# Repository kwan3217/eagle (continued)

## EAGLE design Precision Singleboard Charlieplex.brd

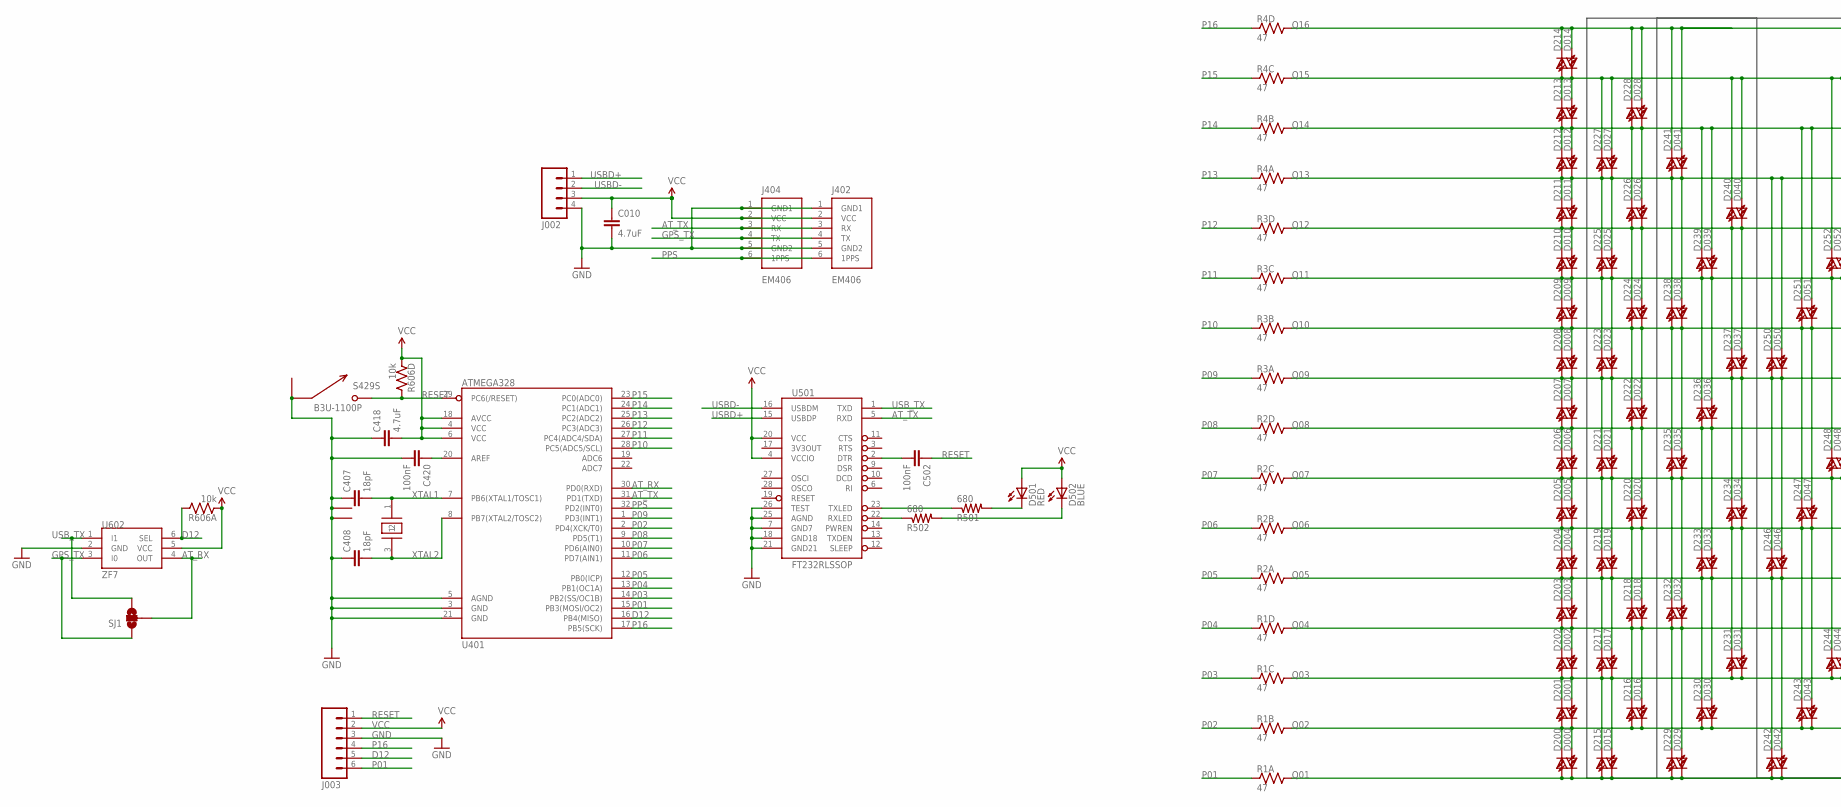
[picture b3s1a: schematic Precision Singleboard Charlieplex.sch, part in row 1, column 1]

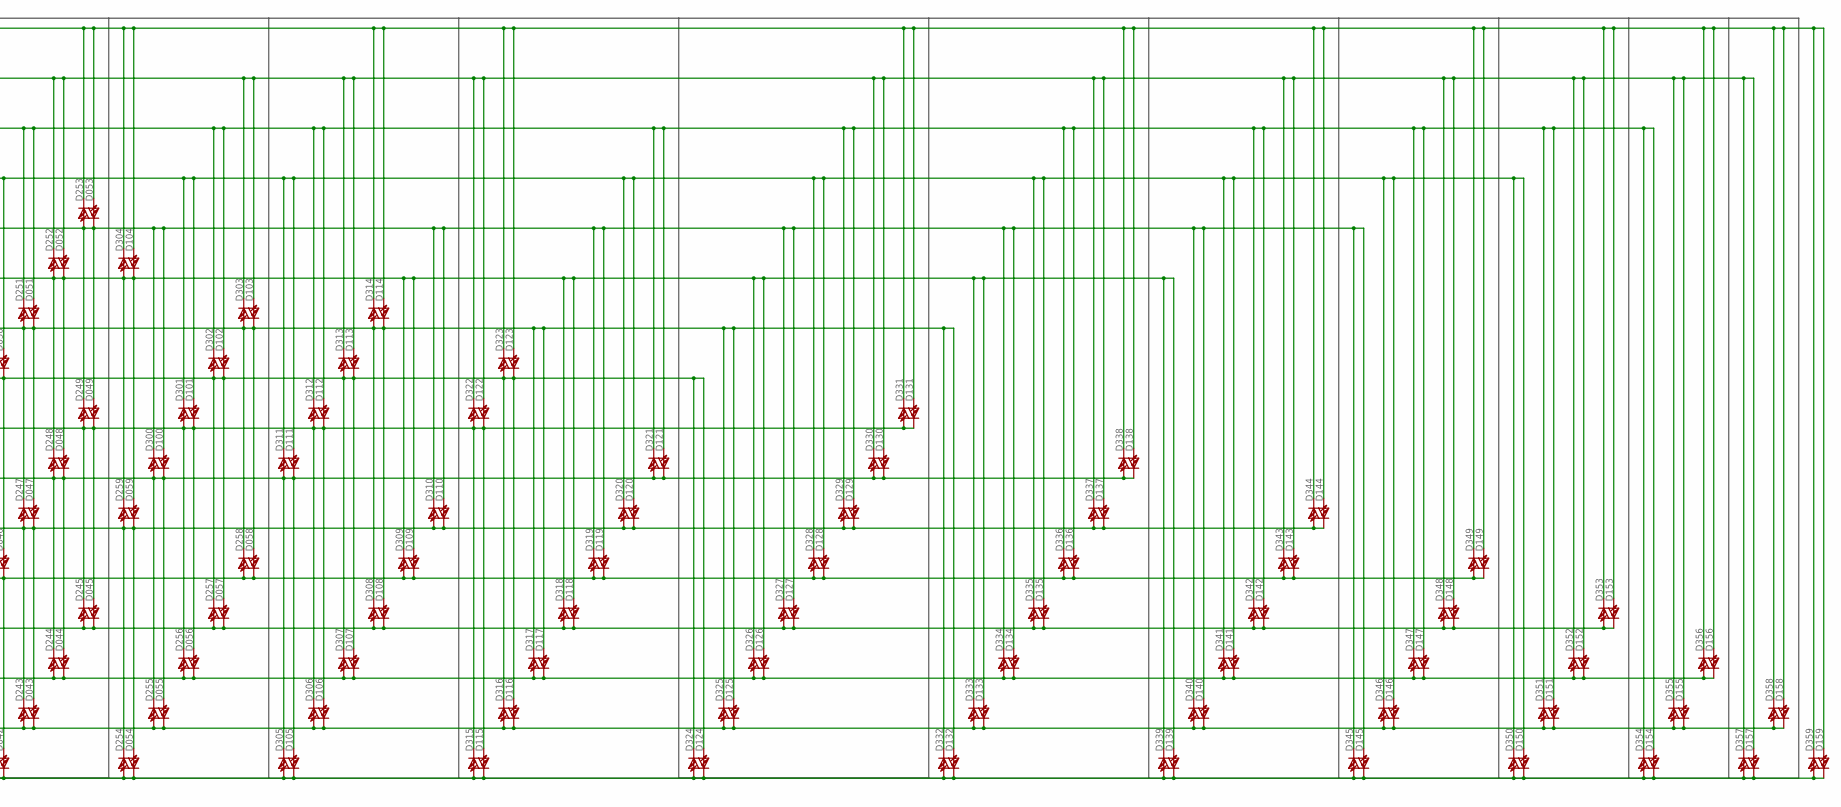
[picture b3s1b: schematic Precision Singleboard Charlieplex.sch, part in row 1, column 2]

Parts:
C010, C418: 4.7uF; 0603-CAP
C407, C408: 18pF; 0603-CAP
C420, C502: 100nF; 0603-CAP
D000, D001, D002, D003, D004, D005, D006, D007, D008, D009, D010, D011, D012, D013, D014, D015, D016, D017, D018, D019, D020, D021, D022, D023, D024, D025, D026, D027, D028, D029, D030, D031, D032, D033, D034, D035, D036, D037, D038, D039, D040, D041, D042, D043, D044, D045, D046, D047, D048, D049, D050, D051, D052, D053, D054, D055, D056, D057, D058, D059, D100, D101, D102, D103, D104, D105, D106, D107, D108, D109, D110, D111, D112, D113, D114, D115, D116, D117, D118, D119, D120, D121, D122, D123, D124, D125, D126, D127, D128, D129, D130, D131, D132, D133, D134, D135, D136, D137, D138, D139, D140, D141, D142, D143, D144, D145, D146, D147, D148, D149, D150, D151, D152, D153, D154, D155, D156, D157, D158, D159, D200, D201, D202, D203, D204, D205, D206, D207, D208, D209, D210, D211, D212, D213, D214, D215, D216, D217, D218, D219, D220, D221, D222, D223, D224, D225, D226, D227, D228, D229, D230, D231, D232, D233, D234, D235, D236, D237, D238, D239, D240, D241, D242, D243, D244, D245, D246, D247, D248, D249, D250, D251, D252, D253, D254, D255, D256, D257, D258, D259, D300, D301, D302, D303, D304, D305, D306, D307, D308, D309, D310, D311, D312, D313, D314, D315, D316, D317, D318, D319, D320, D321, D322, D323, D324, D325, D326, D327, D328, D329, D330, D331, D332, D333, D334, D335, D336, D337, D338, D339, D340, D341, D342, D343, D344, D345, D346, D347, D348, D349, D350, D351, D352, D353, D354, D355, D356, D357, D358, D359: HOUR; LED-0603
D501: RED; LED-0603
D502: BLUE; LED-0603
J002: M04PTH; 1X04
J003: M06SIP; 1X06
J402, J404: EM406
R1, R2, R3, R4: 47; CRA04
R501, R502: 680; 0603-RES
R606: 10k; CRA04
S429: B3U-1100P
SJ1: SOLDERJUMPER_2WAYS; SJ_3
U401: ATMEGA328; TQFP32-08
U501: FT232RLSSOP; SSOP28DB
U602: ZF7; SC-70-6
Y401: 12.00; CRYSTAL_SMD

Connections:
AREF: C420.1, U401.20 (AREF)
AT_RX: SJ1.2, U401.30 (PD0(RXD)), U602.4 (OUT)
AT_TX: J402.3 (RX), J404.3 (RX), U401.31 (PD1(TXD)), U501.5 (RXD)
D12: J003.5, R606.8 (2), U401.16 (PB4(MISO)), U602.6 (SEL)
GND: C010.2, C407.1, C408.1, C418.1, C420.2, J002.4, J003.3, J402.1 (GND1), J402.5 (GND2), J404.1 (GND1), J404.5 (GND2), S429.P$1 (1), S429.P$3 (1), U401.3 (GND), U401.5 (AGND), U401.21 (GND), U501.7 (GND7), U501.18 (GND18), U501.21 (GND21), U501.25 (AGND), U501.26 (TEST), U602.2 (GND), Y401.2 (1), Y401.4 (1)
GPS_TX: J402.4 (TX), J404.4 (TX), SJ1.1, U602.3 (I0)
unnamed: C502.2, U501.2 (DTR)
unnamed: D501.C, R501.2
unnamed: R501.1, U501.23 (TXLED)
unnamed: R502.1, U501.22 (RXLED)
unnamed: D502.C, R502.2
P01: J003.6, R1.1, U401.15 (PB3(MOSI/OC2))
P02: R1.2 (1), U401.2 (PD4(XCK/T0))
P03: R1.3 (1), U401.14 (PB2(SS/OC1B))
P04: R1.4 (1), U401.13 (PB1(OC1A))
P05: R2.1, U401.12 (PB0(ICP))
P06: R2.2 (1), U401.11 (PD7(AIN1))
P07: R2.3 (1), U401.10 (PD6(AIN0))
P08: R2.4 (1), U401.9 (PD5(T1))
P09: R3.1, U401.1 (PD3(INT1))
P10: R3.2 (1), U401.28 (PC5(ADC5/SCL))
P11: R3.3 (1), U401.27 (PC4(ADC4/SDA))
P12: R3.4 (1), U401.26 (PC3(ADC3))
P13: R4.1, U401.25 (PC2(ADC2))
P14: R4.2 (1), U401.24 (PC1(ADC1))
P15: R4.3 (1), U401.23 (PC0(ADC0))
P16: J003.4, R4.4 (1), U401.17 (PB5(SCK))
PPS: J402.6 (1PPS), J404.6 (1PPS), U401.32 (PD2(INT0))
Q01: D000.C, D015.C, D029.C, D042.C, D054.C, D105.C, D115.C, D124.C, D132.C, D139.C, D145.C, D150.C, D154.C, D157.C, D159.C, D200.A, D215.A, D229.A, D242.A, D254.A, D305.A, D315.A, D324.A, D332.A, D339.A, D345.A, D350.A, D354.A, D357.A, D359.A, R1.8 (2)
Q02: D000.A, D001.C, D016.C, D030.C, D043.C, D055.C, D106.C, D116.C, D125.C, D133.C, D140.C, D146.C, D151.C, D155.C, D158.C, D200.C, D201.A, D216.A, D230.A, D243.A, D255.A, D306.A, D316.A, D325.A, D333.A, D340.A, D346.A, D351.A, D355.A, D358.A, R1.7 (2)
Q03: D001.A, D002.C, D015.A, D017.C, D031.C, D044.C, D056.C, D107.C, D117.C, D126.C, D134.C, D141.C, D147.C, D152.C, D156.C, D201.C, D202.A, D215.C, D217.A, D231.A, D244.A, D256.A, D307.A, D317.A, D326.A, D334.A, D341.A, D347.A, D352.A, D356.A, R1.6 (2)
Q04: D002.A, D003.C, D016.A, D018.C, D029.A, D032.C, D045.C, D057.C, D108.C, D118.C, D127.C, D135.C, D142.C, D148.C, D153.C, D202.C, D203.A, D216.C, D218.A, D229.C, D232.A, D245.A, D257.A, D308.A, D318.A, D327.A, D335.A, D342.A, D348.A, D353.A, R1.5 (2)
Q05: D003.A, D004.C, D017.A, D019.C, D030.A, D033.C, D042.A, D046.C, D058.C, D109.C, D119.C, D128.C, D136.C, D143.C, D149.C, D203.C, D204.A, D217.C, D219.A, D230.C, D233.A, D242.C, D246.A, D258.A, D309.A, D319.A, D328.A, D336.A, D343.A, D349.A, R2.8 (2)
Q06: D004.A, D005.C, D018.A, D020.C, D031.A, D034.C, D043.A, D047.C, D054.A, D059.C, D110.C, D120.C, D129.C, D137.C, D144.C, D204.C, D205.A, D218.C, D220.A, D231.C, D234.A, D243.C, D247.A, D254.C, D259.A, D310.A, D320.A, D329.A, D337.A, D344.A, R2.7 (2)
Q07: D005.A, D006.C, D019.A, D021.C, D032.A, D035.C, D044.A, D048.C, D055.A, D100.C, D105.A, D111.C, D121.C, D130.C, D138.C, D205.C, D206.A, D219.C, D221.A, D232.C, D235.A, D244.C, D248.A, D255.C, D300.A, D305.C, D311.A, D321.A, D330.A, D338.A, R2.6 (2)
Q08: D006.A, D007.C, D020.A, D022.C, D033.A, D036.C, D045.A, D049.C, D056.A, D101.C, D106.A, D112.C, D115.A, D122.C, D131.C, D206.C, D207.A, D220.C, D222.A, D233.C, D236.A, D245.C, D249.A, D256.C, D301.A, D306.C, D312.A, D315.C, D322.A, D331.A, R2.5 (2)
Q09: D007.A, D008.C, D021.A, D023.C, D034.A, D037.C, D046.A, D050.C, D057.A, D102.C, D107.A, D113.C, D116.A, D123.C, D124.A, D207.C, D208.A, D221.C, D223.A, D234.C, D237.A, D246.C, D250.A, D257.C, D302.A, D307.C, D313.A, D316.C, D323.A, D324.C, R3.8 (2)
Q10: D008.A, D009.C, D022.A, D024.C, D035.A, D038.C, D047.A, D051.C, D058.A, D103.C, D108.A, D114.C, D117.A, D125.A, D132.A, D208.C, D209.A, D222.C, D224.A, D235.C, D238.A, D247.C, D251.A, D258.C, D303.A, D308.C, D314.A, D317.C, D325.C, D332.C, R3.7 (2)
Q11: D009.A, D010.C, D023.A, D025.C, D036.A, D039.C, D048.A, D052.C, D059.A, D104.C, D109.A, D118.A, D126.A, D133.A, D139.A, D209.C, D210.A, D223.C, D225.A, D236.C, D239.A, D248.C, D252.A, D259.C, D304.A, D309.C, D318.C, D326.C, D333.C, D339.C, R3.6 (2)
Q12: D010.A, D011.C, D024.A, D026.C, D037.A, D040.C, D049.A, D053.C, D100.A, D110.A, D119.A, D127.A, D134.A, D140.A, D145.A, D210.C, D211.A, D224.C, D226.A, D237.C, D240.A, D249.C, D253.A, D300.C, D310.C, D319.C, D327.C, D334.C, D340.C, D345.C, R3.5 (2)
Q13: D011.A, D012.C, D025.A, D027.C, D038.A, D041.C, D050.A, D101.A, D111.A, D120.A, D128.A, D135.A, D141.A, D146.A, D150.A, D211.C, D212.A, D225.C, D227.A, D238.C, D241.A, D250.C, D301.C, D311.C, D320.C, D328.C, D335.C, D341.C, D346.C, D350.C, R4.8 (2)
Q14: D012.A, D013.C, D026.A, D028.C, D039.A, D051.A, D102.A, D112.A, D121.A, D129.A, D136.A, D142.A, D147.A, D151.A, D154.A, D212.C, D213.A, D226.C, D228.A, D239.C, D251.C, D302.C, D312.C, D321.C, D329.C, D336.C, D342.C, D347.C, D351.C, D354.C, R4.7 (2)
Q15: D013.A, D014.C, D027.A, D040.A, D052.A, D103.A, D113.A, D122.A, D130.A, D137.A, D143.A, D148.A, D152.A, D155.A, D157.A, D213.C, D214.A, D227.C, D240.C, D252.C, D303.C, D313.C, D322.C, D330.C, D337.C, D343.C, D348.C, D352.C, D355.C, D357.C, R4.6 (2)
Q16: D014.A, D028.A, D041.A, D053.A, D104.A, D114.A, D123.A, D131.A, D138.A, D144.A, D149.A, D153.A, D156.A, D158.A, D159.A, D214.C, D228.C, D241.C, D253.C, D304.C, D314.C, D323.C, D331.C, D338.C, D344.C, D349.C, D353.C, D356.C, D358.C, D359.C, R4.5 (2)
RESET: C502.1, J003.1, R606.5 (2), S429.P$2 (2), U401.29 (PC6(/RESET))
USBD+: J002.1, U501.15 (USBDP)
USBD-: J002.2, U501.16 (USBDM)
USB_TX: SJ1.3, U501.1 (TXD), U602.1 (I1)
VCC: C010.1, C418.2, D501.A, D502.A, J002.3, J003.2, J402.2 (VCC), J404.2 (VCC), R606.1, R606.4 (1), U401.4 (VCC), U401.6 (VCC), U401.18 (AVCC), U501.4 (VCCIO), U501.20 (VCC), U602.5 (VCC)
XTAL1: C407.2, U401.7 (PB6(XTAL1/TOSC1)), Y401.1
XTAL2: C408.2, U401.8 (PB7(XTAL2/TOSC2)), Y401.3 (2)

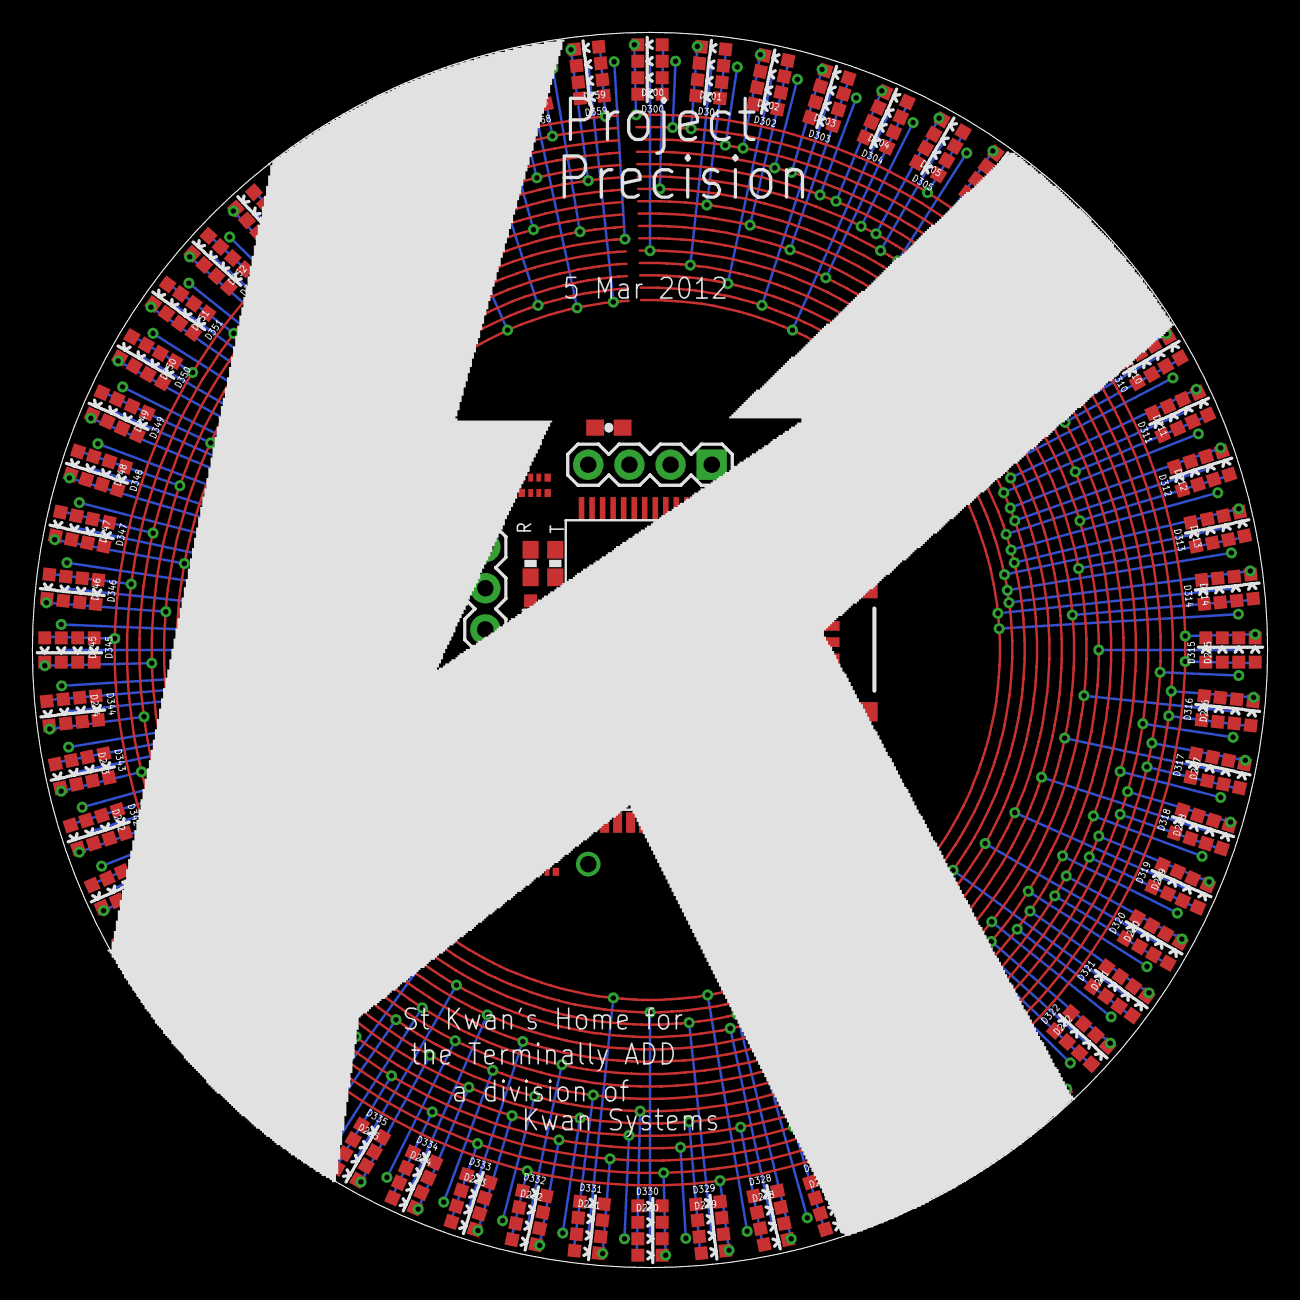
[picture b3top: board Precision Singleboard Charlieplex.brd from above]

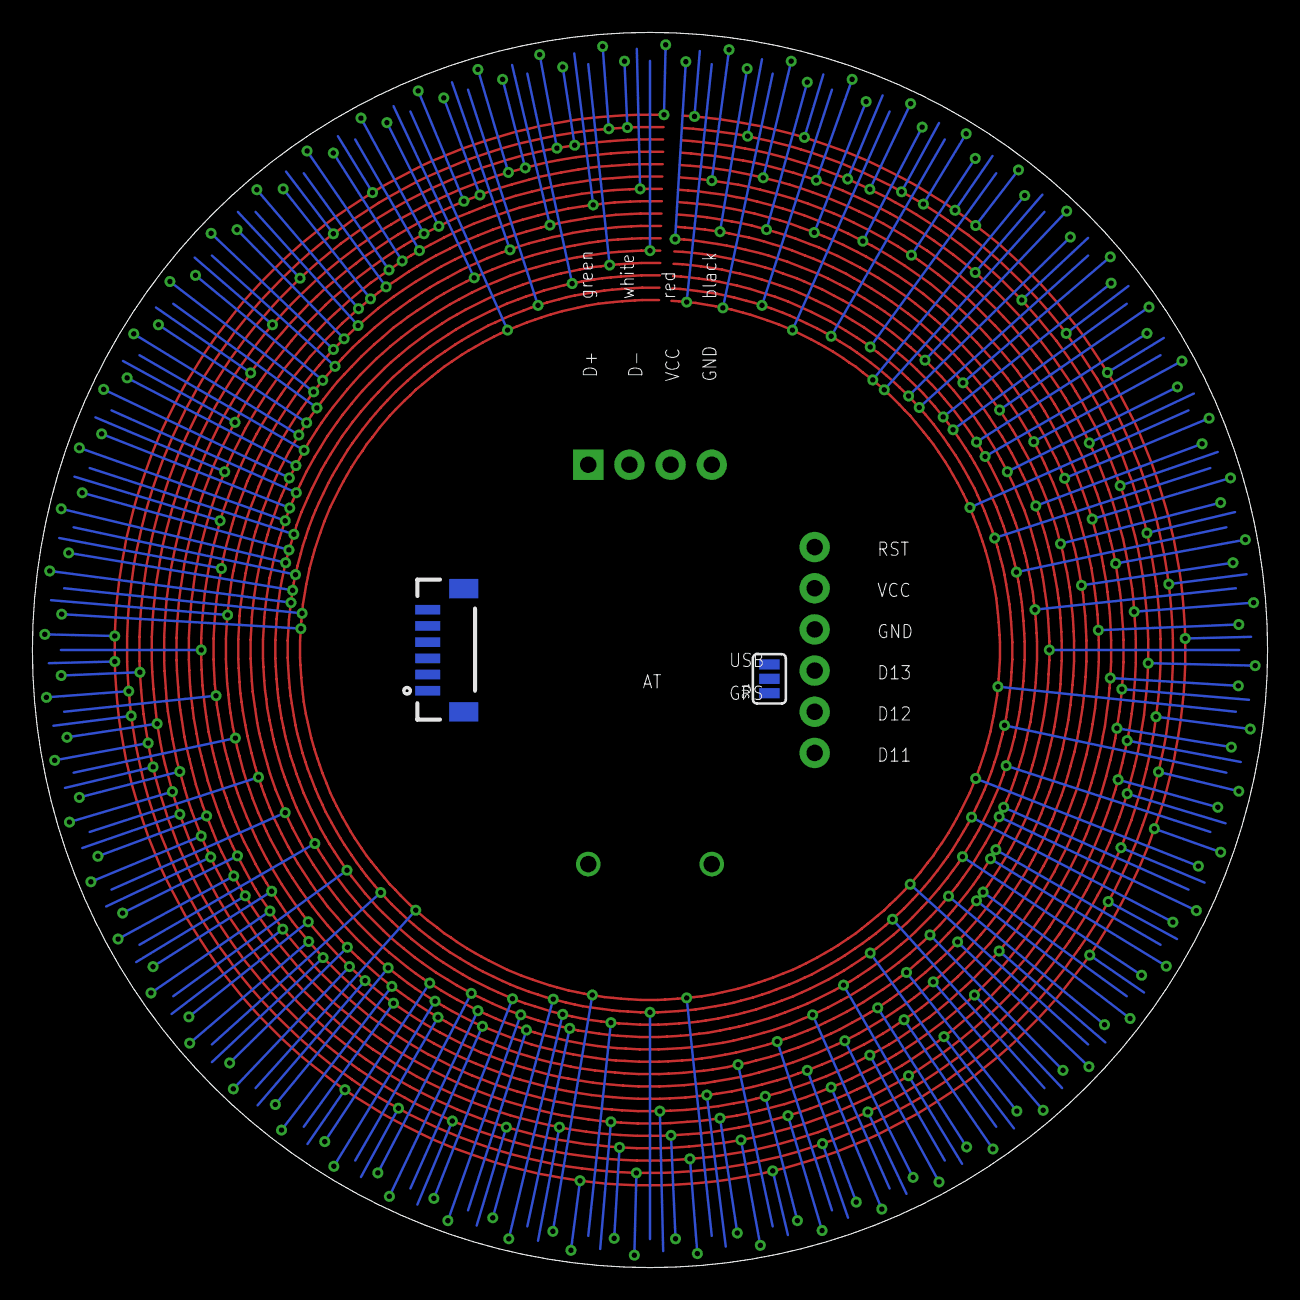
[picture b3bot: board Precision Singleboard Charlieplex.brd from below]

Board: 2 copper layers, 76.2 x 76.2 mm, 265 parts (2 on the bottom side), 51 nets.

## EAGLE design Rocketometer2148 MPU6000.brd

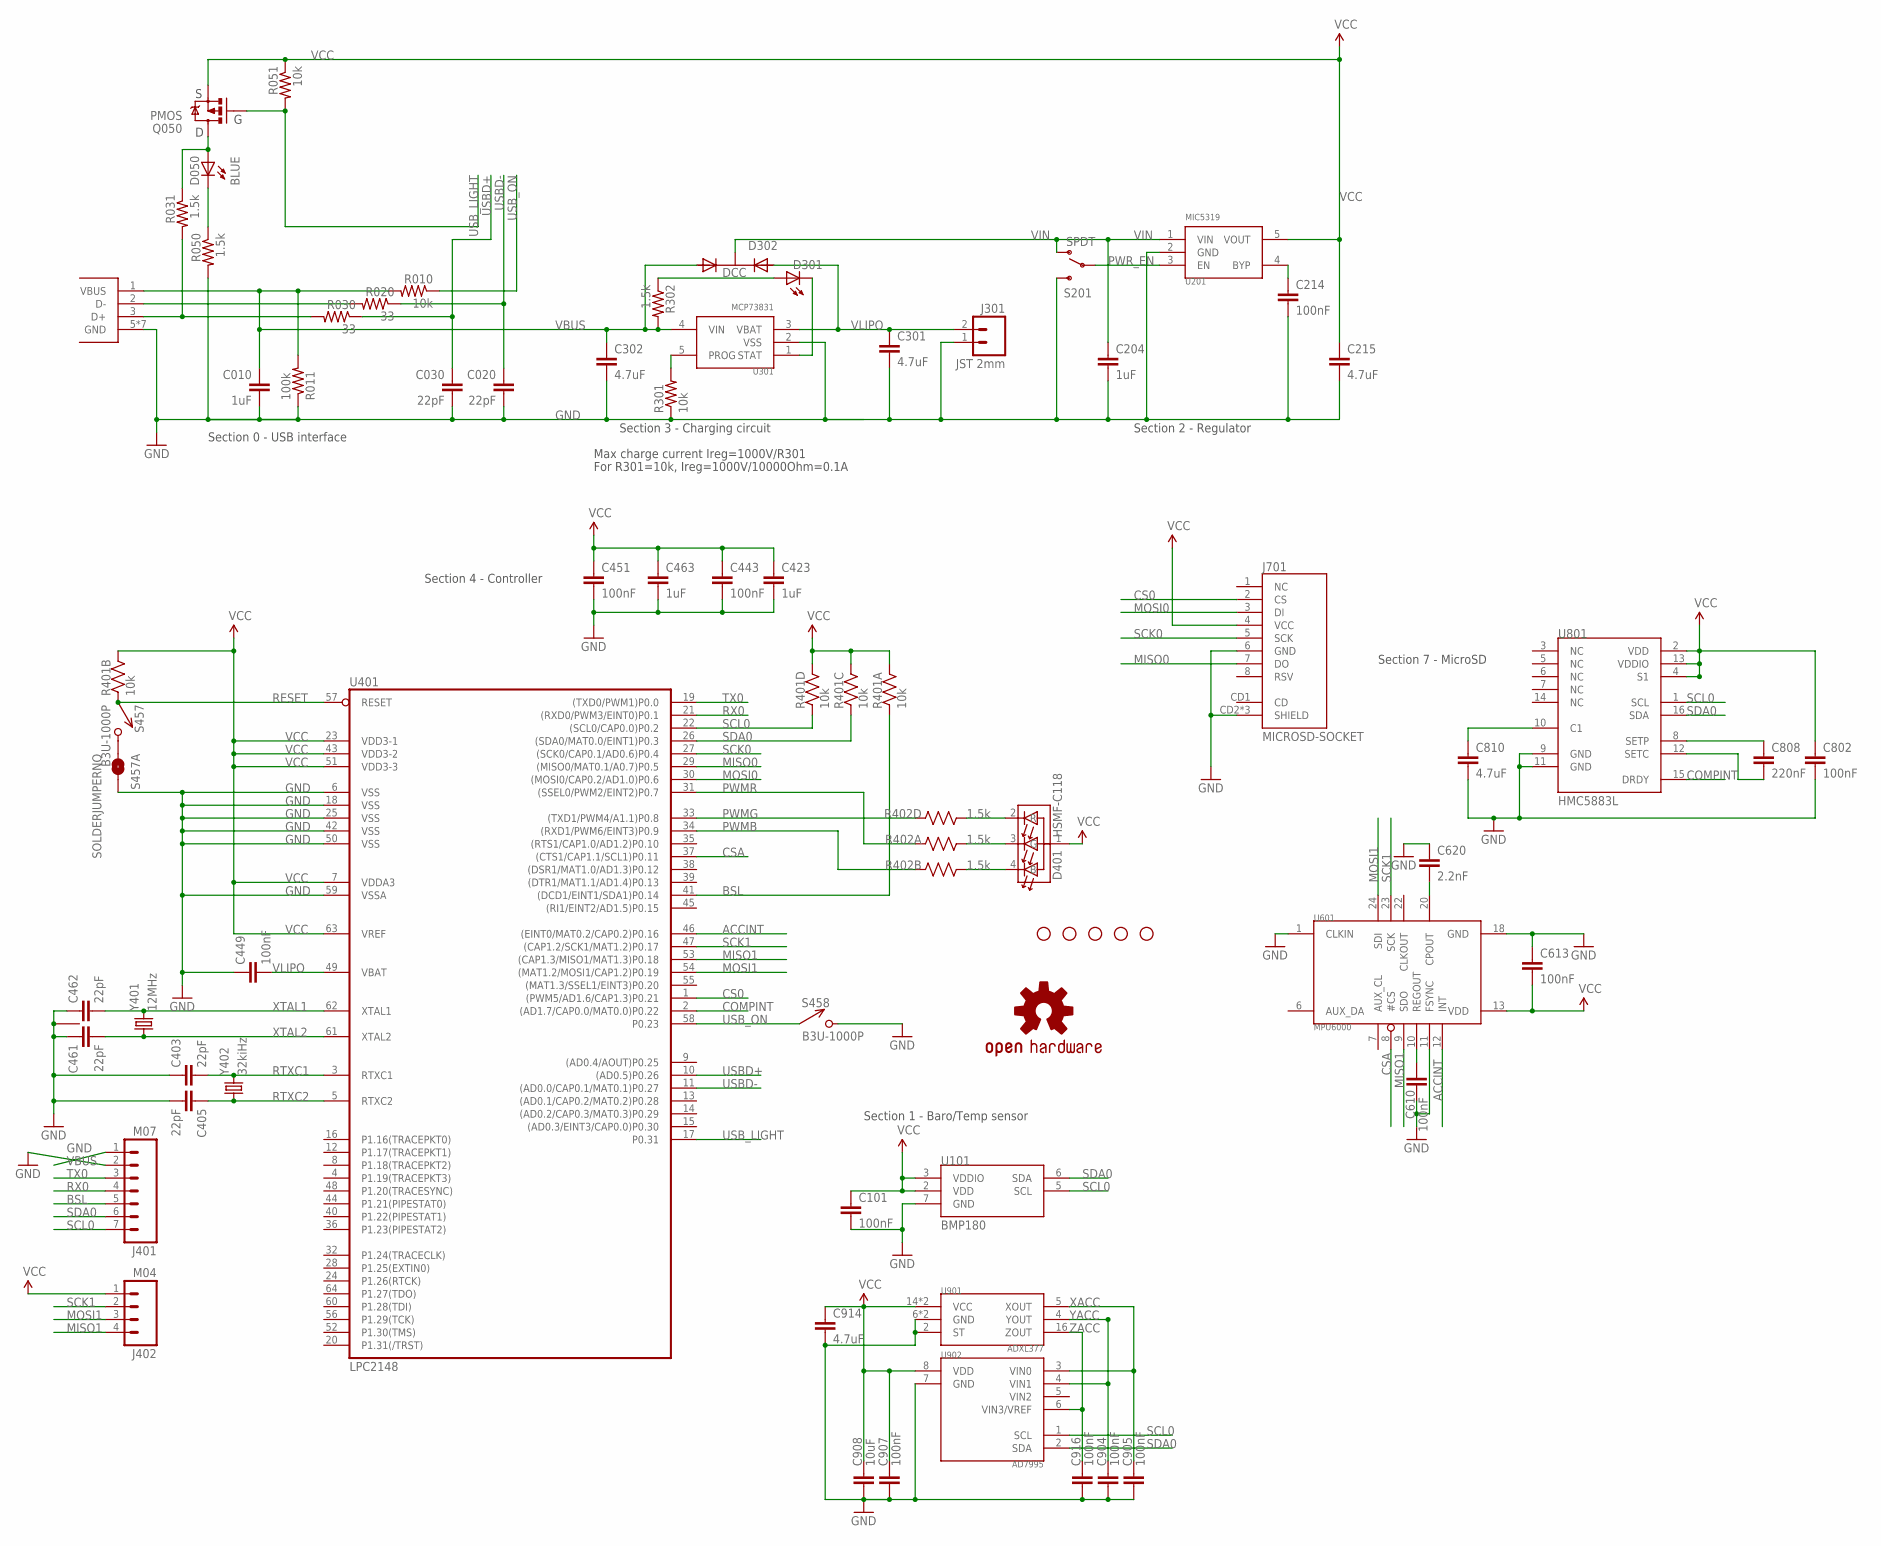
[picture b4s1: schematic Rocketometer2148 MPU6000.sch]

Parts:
C010, C204: 1uF; 0402-CAP; DIGIKEY 445-1415-1-ND
C020, C030, C403, C405, C461, C462: 22pF; 0402-CAP; DIGIKEY 445-1239-1-ND
C101, C214, C443, C449, C451, C610, C613, C802, C904, C905, C916: 100nF; 0402-CAP; DIGIKEY 445-1268-1-ND
C215, C301, C302, C810, C914: 4.7uF; 0402-CAP; DIGIKEY 445-7395-1-ND
C423, C463: 1uF; 0402-CAP; DIGIKEY 445-1268-1-ND
C620: 2.2nF; 0402-CAP; DIGIKEY 445-4976-1-ND
C808: 220nF; 0402-CAP; DIGIKEY 445-4972-1-ND
C907: 100nF; 0402-CAP; DIGIKEY 445-1316-1-ND
C908: 10uF; 0603-CAP; DIGIKEY 445-7486-1-ND
D050: BLUE; LED-0603; DIGIKEY 350-2037-1-ND
D301: YELLOW; LED-0603; DIGIKEY 754-1124-1-ND
D302: DCC; SOT-23-3; DIGIKEY 568-6500-1-ND
D401: HSMF-C118; DIGIKEY 516-1778-1-ND
J001: USB_MICROB_JST; UB-MC5BR3-SD204-4S; DIGIKEY 455-2562-1-ND
J301: JST 2mm; JST-2-SMD; DIGIKEY 455-1749-1-ND
J401: M07; 1X07; DIGIKEY $NOPART
J402: M04; 1X04; DIGIKEY $NOPART
J701: MICROSD-SOCKET; MICROSD-SOCKET-PP; DIGIKEY 101-00581-59-1-ND
JP1, JP2, JP3, JP4, JP5: STAND-OFFTIGHT; STAND-OFF-TIGHT; DIGIKEY $NOPART
Q050: PMOS; SOT23-3; DIGIKEY NTR1P02T1GOSCT-ND
R010, R051, R301: 10k; 0402-RES; DIGIKEY P10.0KLCT-ND
R011: 100k; 0402-RES; DIGIKEY P100KLCT-ND
R020, R030: 33; 0402-RES; DIGIKEY P33.0LCT-ND
R031, R050, R302: 1.5k; 0402-RES; DIGIKEY P1.50KLCT-ND
R401: 10k; CRA04; DIGIKEY CRA4S810KCT-ND
R402: 1.5k; CRA04; DIGIKEY CRA4S81.5KCT-ND
S201: SPDT; AYZ0202; DIGIKEY 401-2013-1-ND
S457, S458: B3U-1000P; DIGIKEY SW1020CT-ND
S457A: SOLDERJUMPERNO; SJ_2S-NO; DIGIKEY $NOPART
U101: BMP180; DIGIKEY 828-1027-1-ND
U201: MIC5319; SOT-23-5; DIGIKEY 576-1910-1-ND
U301: MCP73831; SOT-23-5; DIGIKEY MCP73831T-2ACI/OTCT-ND
U401: LPC2148; SQFP-S-10X10-64; DIGIKEY 568-1765-ND
U601: MPU6000; MPU60X0
U801: HMC5883L; 16LPCC; DIGIKEY 342-1082-1-ND
U901: ADXL377
U902: AD7995; SOT-23-8; DIGIKEY AD7995YRJZ-1500RL7CT-ND
U$2: OSHW-LOGOS; OSHW-LOGO-S; DIGIKEY $NOPART
Y401: 12MHz; CRYSTAL_SMD_2MM_2_5MM
Y402: 32kiHz; ABS06; DIGIKEY 535-10248-1-ND

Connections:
ACCINT: U401.46 ((EINT0/MAT0.2/CAP0.2)P0.16), U601.12 (INT)
BSL: J401.5, R401.1, U401.41 ((DCD1/EINT1/SDA1)P0.14)
COMPINT: U401.2 ((AD1.7/CAP0.0/MAT0.0)P0.22), U801.15 (DRDY)
CONN_D+: J001.3 (D+), R030.2, R031.2
CONN_D-: J001.2 (D-), R020.2
CS0: J701.2 (CS), U401.1 ((PWM5/AD1.6/CAP1.3)P0.21)
CSA: U401.37 ((CTS1/CAP1.1/SCL1)P0.11), U601.8 (#CS)
GND: C010.2, C020.2, C030.2, C101.2, C204.2, C214.2, C215.2, C301.2, C302.2, C403.1, C405.2, C423.2, C443.2, C449.1, C451.2, C461.1, C462.1, C463.2, C610.2, C613.1, C620.1, C802.2, C810.2, C904.2, C905.2, C907.2, C908.2, C914.2, C916.2, J001.5 (GND), J001.P$6 (GND), J001.P$7 (GND), J001.P$8 (GND), J001.P$9 (GND), J001.P$10 (GND), J001.P$11 (GND), J301.1, J401.2, J701.6 (GND), J701.CD2 (SHIELD), J701.GND1 (SHIELD), J701.GND3 (SHIELD), R011.1, R050.2, R301.1, S201.3 (S), S457A.2, S458.P$2 (2), U101.7 (GND), U201.2 (GND), U301.2 (VSS), U401.6 (VSS), U401.18 (VSS), U401.25 (VSS), U401.42 (VSS), U401.50 (VSS), U401.59 (VSSA), U601.1 (CLKIN), U601.11 (FSYNC), U601.18 (GND), U801.9 (GND), U801.11 (GND), U901.2 (ST), U901.6 (GND), U901.7 (GND), U902.7 (GND), Y401.2 (1), Y401.4 (1)
MISO0: J701.7 (DO), U401.29 ((MISO0/MAT0.1/A0.7)P0.5)
MISO1: J402.4, U401.53 ((CAP1.3/MISO1/MAT1.3)P0.18), U601.9 (SDO)
MOSI0: J701.3 (DI), U401.30 ((MOSI0/CAP0.2/AD1.0)P0.6)
MOSI1: J402.3, U401.54 ((MAT1.2/MOSI1/CAP1.2)P0.19), U601.24 (SDI)
unnamed: C620.2, U601.20 (CPOUT)
unnamed: R301.2, U301.5 (PROG)
unnamed: D401.4 (B), R402.2 (1)
unnamed: D301.C, U301.1 (STAT)
unnamed: D301.A, R302.1
unnamed: D050.A, Q050.3 (D), R031.1
unnamed: D050.C, R050.1
unnamed: S457.P$2 (2), S457A.1
unnamed: D401.2 (R), R402.4 (1)
unnamed: D401.3 (G), R402.1
unnamed: C610.1, U601.10 (REGOUT)
unnamed: C808.1, U801.8 (SETP)
unnamed: C808.2, U801.12 (SETC)
unnamed: C810.1, U801.10 (C1)
unnamed: C214.1, U201.4 (BYP)
PWMB: R402.7 (2), U401.34 ((RXD1/PWM6/EINT3)P0.9)
PWMG: R402.5 (2), U401.33 ((TXD1/PWM4/A1.1)P0.8)
PWMR: R402.8 (2), U401.31 ((SSEL0/PWM2/EINT2)P0.7)
PWR_EN: S201.2, U201.3 (EN)
RESET: R401.2 (1), S457.P$1 (1), U401.57 (RESET)
RTXC1: C403.2, U401.3 (RTXC1), Y402.2
RTXC2: C405.1, U401.5 (RTXC2), Y402.1
RX0: J401.4, U401.21 ((RXD0/PWM3/EINT0)P0.1)
SCK0: J701.5 (SCK), U401.27 ((SCK0/CAP0.1/AD0.6)P0.4)
SCK1: J402.2, U401.47 ((CAP1.2/SCK1/MAT1.2)P0.17), U601.23 (SCK)
SCL0: J401.7, R401.4 (1), U101.5 (SCL), U401.22 ((SCL0/CAP0.0)P0.2), U801.1 (SCL), U902.1 (SCL)
SDA0: J401.6, R401.3 (1), U101.6 (SDA), U401.26 ((SDA0/MAT0.0/EINT1)P0.3), U801.16 (SDA), U902.2 (SDA)
TX0: J401.3, U401.19 ((TXD0/PWM1)P0.0)
USBD+: C030.1, R030.1, U401.10 ((AD0.5)P0.26)
USBD-: C020.1, R020.1, U401.11 ((AD0.0/CAP0.1/MAT0.1)P0.27)
USB_LIGHT: Q050.1 (G), R051.2, U401.17 (P0.31)
USB_ON: R010.1, S458.P$1 (1), U401.58 (P0.23)
VBUS: C010.1, C302.1, D302.1 (A1), J001.1 (VBUS), J401.1, R010.2, R011.2, R302.2, U301.4 (VIN)
VCC: C101.1, C215.1, C423.1, C443.1, C451.1, C463.1, C613.2, C802.1, C907.1, C908.1, C914.1, D401.1 (A), J402.1, J701.4 (VCC), Q050.2 (S), R051.1, R401.5 (2), R401.6 (2), R401.7 (2), R401.8 (2), U101.2 (VDD), U101.3 (VDDIO), U201.5 (VOUT), U401.7 (VDDA3), U401.23 (VDD3-1), U401.43 (VDD3-2), U401.51 (VDD3-3), U401.63 (VREF), U601.13 (VDD), U801.2 (VDD), U801.4 (S1), U801.13 (VDDIO), U901.14 (VCC), U901.15 (VCC), U902.8 (VDD)
VIN: C204.1, D302.3 (K), S201.1 (O), U201.1 (VIN)
VLIPO: C301.1, C449.2, D302.2 (A2), J301.2, U301.3 (VBAT), U401.49 (VBAT)
XACC: C905.1, U901.5 (XOUT), U902.3 (VIN0)
XTAL1: C462.2, U401.62 (XTAL1), Y401.3 (2)
XTAL2: C461.2, U401.61 (XTAL2), Y401.1
YACC: C904.1, U901.4 (YOUT), U902.4 (VIN1)
ZACC: C916.1, U901.16 (ZOUT), U902.6 (VIN3/VREF)

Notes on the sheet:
Section 2 - Regulator
Section 3 - Charging circuit
Section 0 - USB interface
Section 4 - Controller
Section 7 - MicroSD
Section 1 - Baro/Temp sensor
Max charge current Ireg=1000V/R301
For R301=10k, Ireg=1000V/10000Ohm=0.1A

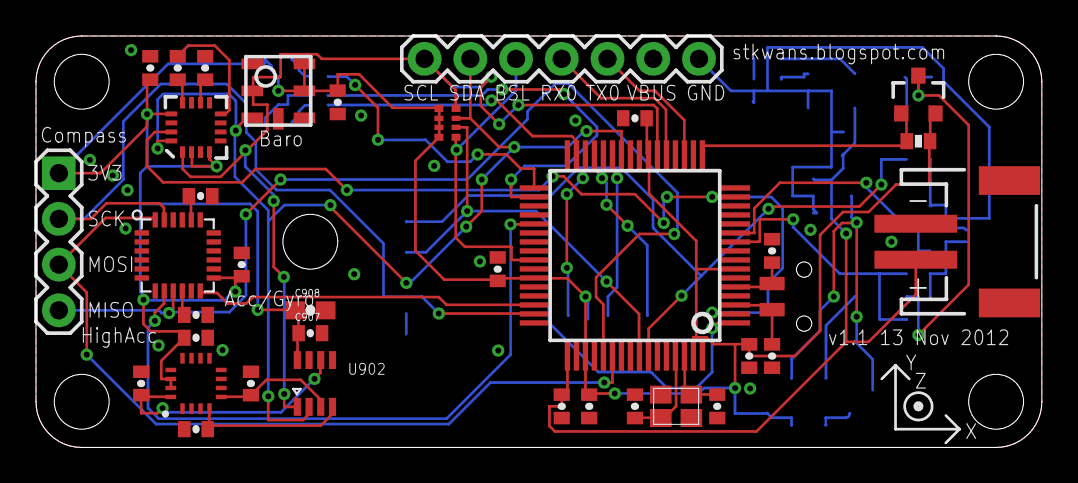
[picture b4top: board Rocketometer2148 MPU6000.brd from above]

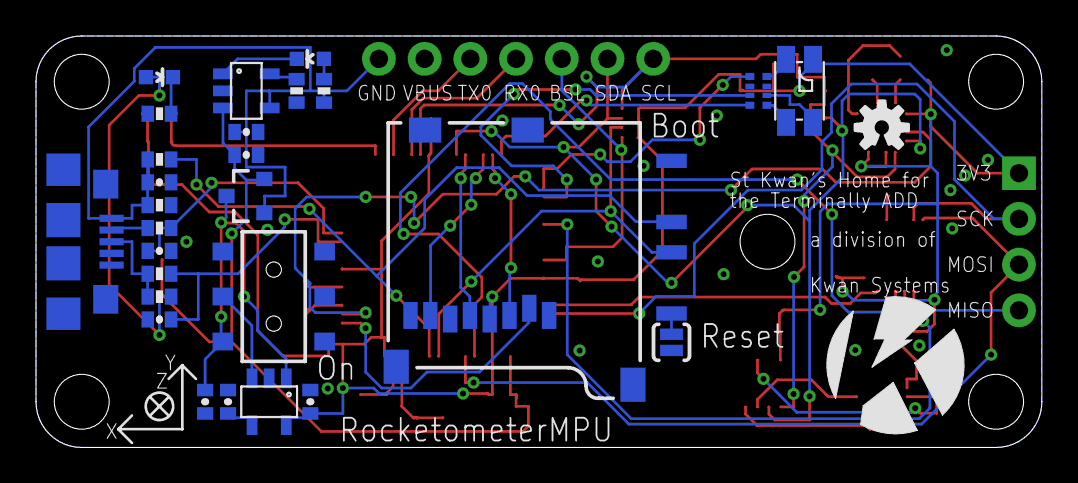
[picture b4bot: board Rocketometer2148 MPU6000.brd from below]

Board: 2 copper layers, 55.9 x 22.9 mm, 73 parts (31 on the bottom side), 53 nets.

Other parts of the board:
U$1: KWAN_CIRCLE
U$4: AXES

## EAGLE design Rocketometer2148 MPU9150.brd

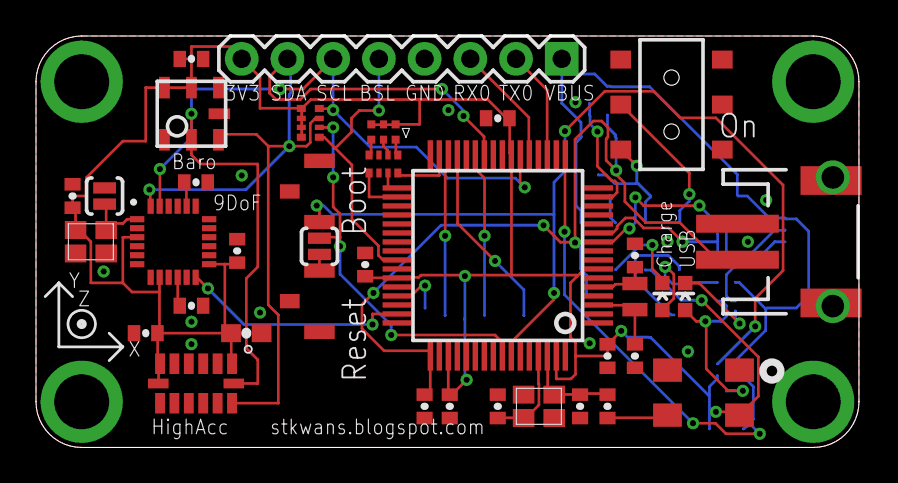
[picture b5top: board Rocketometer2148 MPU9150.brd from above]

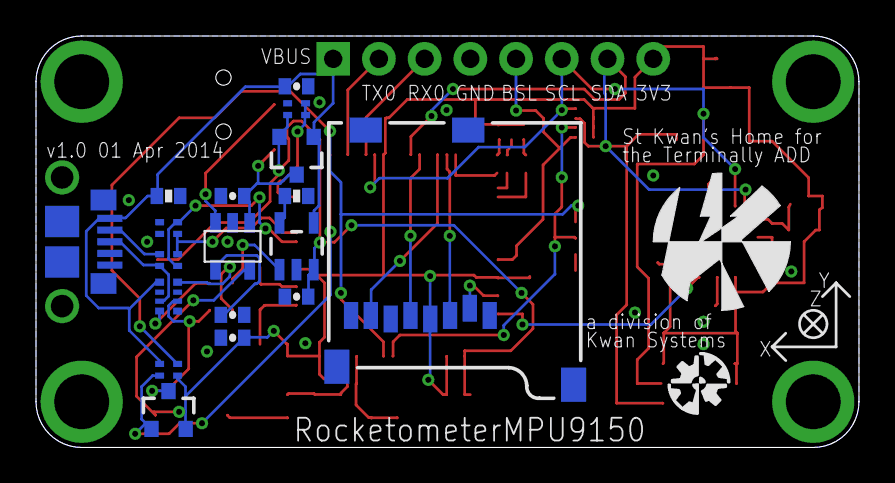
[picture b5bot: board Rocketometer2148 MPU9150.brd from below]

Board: 2 copper layers, 45.7 x 22.9 mm, 62 parts (20 on the bottom side), 45 nets.

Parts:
C023: 22pF; CKCM25
C101, C203, C443, C449, C601, C610, C613, C906: 100nF; 0402-CAP
C201, C301, C302: 4.7uF; 0402-CAP
C204, C423, C451, C463: 1uF; 0402-CAP
C403, C405: 22pF; 0402-CAP
C404: 100pF; 0402-CAP
C461, C462: 33pF; 0402-CAP
C620: 2.2nF; 0402-CAP
C901: 10uF; 0603-CAP
D050: BLUE; LED-0603
D301: YELLOW; LED-0603
D302: DCC; SOT-23-3
D401: SMLP36
J001: USB_MICROB_JSTGCT; USB_MICROB_3075
J301: JST 2mm; JST-2-SMD
J401: M07; 1X08
J701: MICROSD-SOCKET; MICROSD-SOCKET-PP
JP1, JP2, JP4, JP5: STANDOFF
Q050: PMOS; SOT23-3
R011: 100k; 0402-RES
R015: 10k; CRA02
R023: 33; CRA02
R053, R402: 1.5k; CRA04
R301: 10k; 0402-RES
R302: 1M; CRA02
R401: 10k; CRA04
S201: AYZ0202
S457, S458: B3U-1100P
S457A, S457A1: SOLDERJUMPERNO; SJ_2S-NO
U101: BMP180
U201: 5319; SOT-23-5
U301: 73831; SOT23-5
U401: LPC2148; SQFP-S-10X10-64
U601: MPU9150; LLGA24
U902: ADXL375
U$4: AXES
U$5: KWAN_ACC
U$6: OSHW_ACC
Y401: 12MHz; CRYSTAL_SMD_2MM_2_5MM
Y402: 32kiHz; ABS06
Y403: 12MHz; CRYSTAL_SMD_5MM_3_2MM
Y601: 19.2MHz; CRYSTAL_SMD_2MM_2_5MM

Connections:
ACCINT: U401.47, U601.12
BATLVL: R302.3, R302.4, U401.15
BSL: J401.5, R401.1, U401.41
CONN_D+: J001.3, R023.2, R053.7
CONN_D-: J001.2, R023.1
CS0: J701.2, U401.45
EN: S201.5, U201.3
GND: C023.3, C023.4, C101.2, C201.2, C203.2, C204.2, C301.2, C302.2, C403.1, C405.2, C423.2, C443.2, C449.1, C451.2, C461.1, C462.1, C463.2, C601.1, C610.2, C613.1, C620.1, C901.2, C906.2, J001.5, J001.P$1, J001.P$2, J001.P$3, J001.P$4, J001.P$8, J001.P$10, J301.1, J401.4, J701.6, J701.CD2, J701.GND1, J701.GND3, JP1.P$1, JP2.P$1, JP4.P$1, JP5.P$1, R011.1, R053.1, R301.1, R302.1, S201.4, S457.P$2, S457.P$3, S457A1.2, S458.P$1, S458.P$3, U101.7, U201.2, U301.2, U401.6, U401.18, U401.25, U401.42, U401.50, U401.59, U601.9, U601.11, U601.15, U601.17, U601.18, U902.2, U902.4, U902.5, U902.12, Y401.2, Y401.4, Y403.2, Y601.1, Y601.2
MISO0: J701.7, U401.29
MOSI0: J701.3, U401.30
unnamed: C620.2, U601.20
unnamed: R301.2, U301.5
unnamed: D301.A, R053.4
unnamed: D301.C, U301.1
unnamed: C404.2, Y403.3
unnamed: D050.A, Q050.3, R053.2
unnamed: D050.C, R053.8
unnamed: S457.P$1, S457A.2
unnamed: C610.1, U601.10
unnamed: C203.1, U201.4
OSC_9DOF: S457A1.1, U601.1, Y601.3
PWMB: R402.8, U401.31
PWMG: R402.5, U401.34
PWMR: R402.7, U401.33
QWMB: D401.1, R402.1
QWMG: D401.5, R402.4
QWMR: D401.3, R402.2
RESET: R401.2, S457A.1, U401.57
RTXC1: C403.2, U401.3, Y402.2
RTXC2: C405.1, U401.5, Y402.1
RX0: J401.3, U401.21
SCK0: J701.5, U401.27
SCL0: J401.6, R401.4, U101.5, U401.22, U601.23, U902.14
SDA0: J401.7, R401.3, U101.6, U401.26, U601.24, U902.13
TX0: J401.2, U401.19
USBD+: C023.2, R023.3, U401.10
USBD-: C023.1, R023.4, U401.11
USB_ON: R015.2, S458.P$2, U401.58
USB_SOFTCONNECT: Q050.1, R015.4, U401.17
VBUS: C302.1, D302.1, J001.1, J401.1, R011.2, R015.3, R053.5, U301.4
VCC: C101.1, C201.1, C423.1, C443.1, C451.1, C463.1, C601.2, C613.2, C901.1, C906.1, D401.2, D401.4, D401.6, J401.8, J701.4, Q050.2, R015.1, R401.5, R401.6, R401.7, R401.8, U101.2, U101.3, U201.5, U401.7, U401.23, U401.43, U401.51, U401.63, U601.3, U601.8, U601.13, U902.1, U902.6, U902.7, Y403.4, Y601.4
VIN: C204.1, D302.3, S201.6, U201.1
VLIPO: C301.1, C449.2, D302.2, J301.2, R302.2, U301.3, U401.49
XTAL1: C404.1, C462.2, U401.62, Y401.1
XTAL2: C461.2, U401.61, Y401.3
